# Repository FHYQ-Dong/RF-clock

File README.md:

# RF-clock

Two RFSoC 4x2 nodes, each with an SRS FS725 rubidium standard, exchange 5.8 GHz PRN bursts (two-way time transfer, TWTT). The follower steers its FS725 so that its 10 MHz and 1PPS follow the master. The PL keeps time and runs the per-burst measurement chain; the ARM runs the slower algorithms.

New to the project, or to RFSoC and clock measurement: start with the technical report, [docs/technical_report.md](docs/technical_report.md) ([中文](docs/technical_report_zh.md)).

English documents are the reference; `*_zh.md` files are Chinese translations with the same content.

## How it works

- **TWTT.** Nodes A (master) and B (follower) send each other known PRN bursts in fixed slots after each PPS. Each node timestamps the other's burst; differencing the two directions cancels the propagation delay and leaves the clock offset, which drives B's FS725 through its RS-232 port.
- **All of a node's clocks from its FS725.** The FS725 10 MHz drives the board's LMK04828 and LMX2594, which clock the RFDC converters and the PL. The PL counts a raw tick (100 MHz, 10 ns) on that clock, so steering the FS725 moves all of the node's clocks.
- **ARM does algorithms, PL does time and the per-burst measurement chain.** In the PL: the raw tick, PPS capture, the 2 ms slot engine, gap-free TX bursts made from chip sequences through the RRC filter starting at an exact tick, correlation (tracking and search) in every RX window, the measurement packets that carry each node's results to the other inside its bursts, the output PPS, and since 2.5, when chosen, each step of the steering through FC with its command on B's FS725's serial line. On the ARM (Python): the PRN chips and RRC coefficients, clock and RFDC bring-up, acquisition on long windows in DDR, the two-way equations, the steering algorithms that steer B's FS725, and the coefficient tables when the PL steers.
- **Signal.** BPSK PRN at 100 Mchip/s with an RRC filter (β = 0.25), 8 samples per chip at 800 MS/s complex baseband. The DAC runs at 9.6 GS/s and puts the burst at 5.8 GHz (second Nyquist zone); the ADC samples at 4.8 GS/s. RFDC multi-tile sync makes the converter latency the same on every power-up.

The design is in [plan/RF_clock_modules.md](plan/RF_clock_modules.md); the durable constraints any change must respect are in [AGENTS.md](AGENTS.md).

## Status

| Milestone | Result |
| --- | --- |
| M1: raw tick against the FS725 1PPS | Passed: exactly 100,000,000 ticks per second; 3 hours with no PPS jitter or fault count |
| M2: MTS and PPS-timed TX | Passed: every burst starts at its target tick; on a scope the PPS → burst delay is 180.00 ns on every restart |
| M3: wired DAC → ADC loopback | Passed with a cable and attenuator: with both LMX2594 synchronized and their VCO bands forced, the loopback delay holds to 0.1 ps over clock writes and 2.5 hours |
| M4: two-way time transfer between two boards on one reference | θ measured 250 times a second, 0.8 ps per measurement; θ₀ per wiring in `links/` |
| M5: two clocks, B's FS725 steered | θ − θ₀ 5.3–5.6 ps rms per second, steering through FC (2.3.0.2); B's output PPS against A's 9.2 ps rms per second on the scope, the scope's own resolution |
| M6: air link across Long Island Sound | Not started |

Item-by-item results with their evidence: [plan/checklist.md](plan/checklist.md). Results, what limits them and what remains: [docs/technical_report.md](docs/technical_report.md) sections 6–8.

## Hardware

Per node:

| Item | Connection |
| --- | --- |
| Real Digital RFSoC 4x2, PYNQ 3.1.1 image | the board's Linux runs the Python package as root |
| SRS FS725 10 MHz | external reference SMA of the 4x2 (LMK04828 CLKin0) |
| SRS FS725 1PPS | PPS SMA J7 (the board's comparator input) |
| B's FS725 RS-232, for the steering in the PL (2.5) | a TTL-to-RS-232 module (MAX3232, DB-9 male) on J1, the Pmod header, lower row at the PMODB end ([docs/board_setup.md](docs/board_setup.md) section 5.1) |
| RF transmit | DAC_A SMA (`vout20`, DAC tile 2) |
| RF receive | ADC_B SMA (`vin2_01`, ADC tile 2) |
| Loopback test (M3) | DAC_A → SMA cable → ≥ 20 dB attenuator → ADC_B |

Building the bitstream needs Vivado 2024.1 and the [RealDigitalOrg RFSoC4x2-BSP](https://github.com/RealDigitalOrg/RFSoC4x2-BSP) board files.

## Getting started

### On the board

Releases (on GitHub and on the group's Gitea) carry a wheel that contains the library, the bitstream, the clock register files, the examples and the board checks; nothing else from the repository is needed. Install the wheel into PYNQ's own environment as described in [docs/ABI.md §9.1](docs/ABI.md), then, as root:

```bash
run="sudo env BOARD=RFSoC4x2 XILINX_XRT=/usr /usr/local/share/pynq-venv/bin/python"
$run -m rf_clock.checks.vco_bands scan --write  # once per board: the board config,
$run -m rf_clock.checks.mts_dtc record --write   # then its MTS capture windows
$run -m rf_clock.checks.m1_check 60             # tick against the PPS
$run -m rf_clock.checks.m2_tx_timing 10         # MTS and timed bursts
$run -m rf_clock.checks.m3_loopback 20          # loopback delay by correlation
$run -m rf_clock.examples.pl.03_pynq_bringup    # one burst and one RX window
```

The board config, `/etc/rf-clock/board.json`, names its board by serial number and fixes the VCO band of each LMX2594 and the SYSREF capture window of each MTS tile, which otherwise can change from one power-up to the next and move a converter by 8-10 ps or by a whole sample; without them `PL.open()` warns ([docs/ABI.md §11.1](docs/ABI.md)).

A new board, from the SD card to the two-way time transfer, step by step with what each step must show: [docs/board_setup.md](docs/board_setup.md).

In your own code:

```python
from rf_clock.pl import PL, WaveformGenerator

pl = PL.open()                                  # overlay, clocks, MTS, PPS lock
beats = WaveformGenerator().generate_beats()
pl.tx_buffer.write_beats(beats)
_, pps = pl.ctrl.wait_next_pps()
target = pps + 100_000_000 + 100_000            # 1 ms after the next PPS
pl.ctrl.arm_tx(target, len(beats))
pl.ctrl.wait_tx(timeout=2.5)                    # returns TX_ACTUAL == target
```

### On a development machine

```bash
uv sync                               # Python environment (pynq is a dev dependency, for completion only)
uv run pytest                         # unit tests against a fake PL, no hardware
uv run pyright                        # static type check of src, tests, experiments and tools
uv run python -m rf_clock.examples.pl.01_fake_tx
./PL/sim/run_pl_tests.ps1             # RTL testbenches (PowerShell, iverilog)
```

### Building and releasing

1. Set the version in `pyproject.toml` (rules below).
2. On the build machine: `vivado -mode batch -source PL/bd/create_rf_clock_bd.tcl -tclargs <new build dir> <RFSoC4x2-BSP>/board_files impl`
3. `python3 tools/package_overlay.py <build dir>` copies the bitstream and a manifest into `src/rf_clock/overlay/` (refused unless the build completed with timing met for this version).
4. `uv run pytest` and `uv run pyright` pass; commit, then push a tag `vA.B.C.D`: GitHub Actions, and Gitea Actions where the tag is pushed to Gitea, build the wheel and publish a release with notes.

Details in [docs/ABI.md §14.1](docs/ABI.md).

### Versions

The package version `A.B.C.D` binds the Python code to its bitstream:

| Field | Meaning |
| --- | --- |
| A.B | register protocol version (`VERSION` in the PL) |
| C | which bitstream for that protocol |
| D | Python-only releases |

The build writes the version into the bitstream (`BUILD_VERSION`), and `PL.open()` refuses a bitstream whose A.B.C differs from the installed package. A rebuild increments C; a Python-only change increments D.

## Documents

| Document | Content |
| --- | --- |
| [docs/technical_report.md](docs/technical_report.md) ([中文](docs/technical_report_zh.md)) | Technical report and handoff, for readers new to RFSoC and clock measurement: background, design, bench, running and maintaining it, results, the problems found, open work. `pwsh -NoProfile -File tools/build_report.ps1` makes its PDF in `build/` |
| [AGENTS.md](AGENTS.md) | Durable design constraints |
| [plan/RF_clock_modules.md](plan/RF_clock_modules.md) ([中文](plan/RF_clock_modules_zh.md)) | Design plan |
| [plan/checklist.md](plan/checklist.md) ([中文](plan/checklist_zh.md)) | Open items, with evidence for each closed one |
| [docs/ABI.md](docs/ABI.md) ([中文](docs/ABI_zh.md)) | ARM ↔ PL programming manual: registers, timing, power-up, the Python library, board setup, releases |
| [docs/handoff_2x.md](docs/handoff_2x.md) ([中文](docs/handoff_2x_zh.md)) | Moving from 1.x to 2.x: what changed, how to run the link, the metrics before and after and what improved them |
| [docs/board_setup.md](docs/board_setup.md) ([中文](docs/board_setup_zh.md)) | From a new board to one in service: system, installation, wiring, the checks and per-board calibrations in order, what to redo after a change |
| [docs/debug_overview.md](docs/debug_overview.md) ([中文](docs/debug_overview_zh.md)) | Every problem found on the bench, along the 10 MHz distribution: a diagram of each module marking where the problems sat; what was seen, the cause, the change and the version, with links to the reports |
| [src/rf_clock/clocks/files/README.md](src/rf_clock/clocks/files/README.md) | Clock plan and the LMK/LMX register files |

## Layout

| Path | Content |
| --- | --- |
| `PL/src/` | PL RTL (`p_top` and P0–P13); `p_regs.vh` / `p_defs.vh` define the ARM-visible interface |
| `PL/sim/` | iverilog testbenches; run `./PL/sim/run_pl_tests.ps1` |
| `PL/bd/create_rf_clock_bd.tcl` | Vivado 2024.1 block design, synthesis and implementation |
| `PL/constraints/` | RFSoC 4x2 constraints |
| `src/rf_clock/pl/` | ARM ↔ PL interface: power-up, registers, the board config, the slot engine, bursts from chips, the correlator's tracking and search, the measurement queue, acquisition, the output PPS, the FS725's serial line, the steering in the PL; TX buffer, RX DMA, beat codec, waveform generator |
| `src/rf_clock/clocks/` | LMK04828/LMX2594 register files and their decoders |
| `src/rf_clock/overlay/` | The bitstream (`.bit`/`.hwh`/`.xsa`, Git LFS) shipped with the package |
| `src/rf_clock/checks/` | Board checks for milestones M1–M3, one node of the rf-clock 2 link (`m4c_link`), the per-board calibrations (`vco_bands`, `mts_dtc`, `fs725_loop`, `pps_pp_scan`) and the output PPS on its own (`pps_out`) |
| `src/rf_clock/examples/` | Annotated examples: fake PL, board bring-up, one node of the rf-clock 2 link, the two-way equations and the steering on a development machine, raw PYNQ and C++ access |
| `src/rf_clock/correlator.py` | Cross-correlation delay estimation |
| `src/rf_clock/plmodel/` | Bit-exact models of the PL's measurement chain and of its steering through FC, for the RTL testbenches and to recompute the PL's results on the ARM |
| `src/rf_clock/twtt/` | Two-way time transfer between two boards: rf-clock 2's two-way equations from a node's queue (`pairs`), the node's FS725 and SYNCED (`control`), the steering algorithms that steer B's FS725 (`steer`), the node's log read back (`logs`); the 1.x exchange over Ethernet (`timing`, `node`, `link`) |
| `src/rf_clock/fs725.py` | The FS725 rubidium standard over RS-232: status, frequency offset (SF), loop gain (GA), the crystal's tuning (FC), 1 pps time tags and placement |
| `tests/` | Unit tests (pytest, no hardware) |
| `tools/` | ABI generator, overlay packaging, release notes, version snapshots, results backup, the technical report's PDF, JTAG board reset |
| `boards/` | A copy of each board's config (`/etc/rf-clock/board.json`): reference and backup |
| `links/` | θ₀, B's steering target, per pair of boards and wiring ([links/README.md](links/README.md)) |
| `experiments/` | Bench experiments, run on RF-clock-PC: `m<N>_*.py` is a sub-experiment of milestone M<N> (plan section 9), one question each; `m3_common.py` holds what the M3 loopback series share; `epg1.py`, `lnb.py`, `sa_sweep.py` are the bench tools they use (EPG1 PPS distribution, scope .lnb files, SA124B) |
| `.github/workflows/release.yml` | Builds and publishes a GitHub release when a `vA.B.C.D` tag is pushed |
| `.gitea/workflows/release.yml` | The same for a Gitea release, plus an upload to the Gitea PyPI registry (Gitea Actions) |

The bitstream and other binaries are stored with Git LFS: after cloning, run `git lfs install` and `git lfs pull`.

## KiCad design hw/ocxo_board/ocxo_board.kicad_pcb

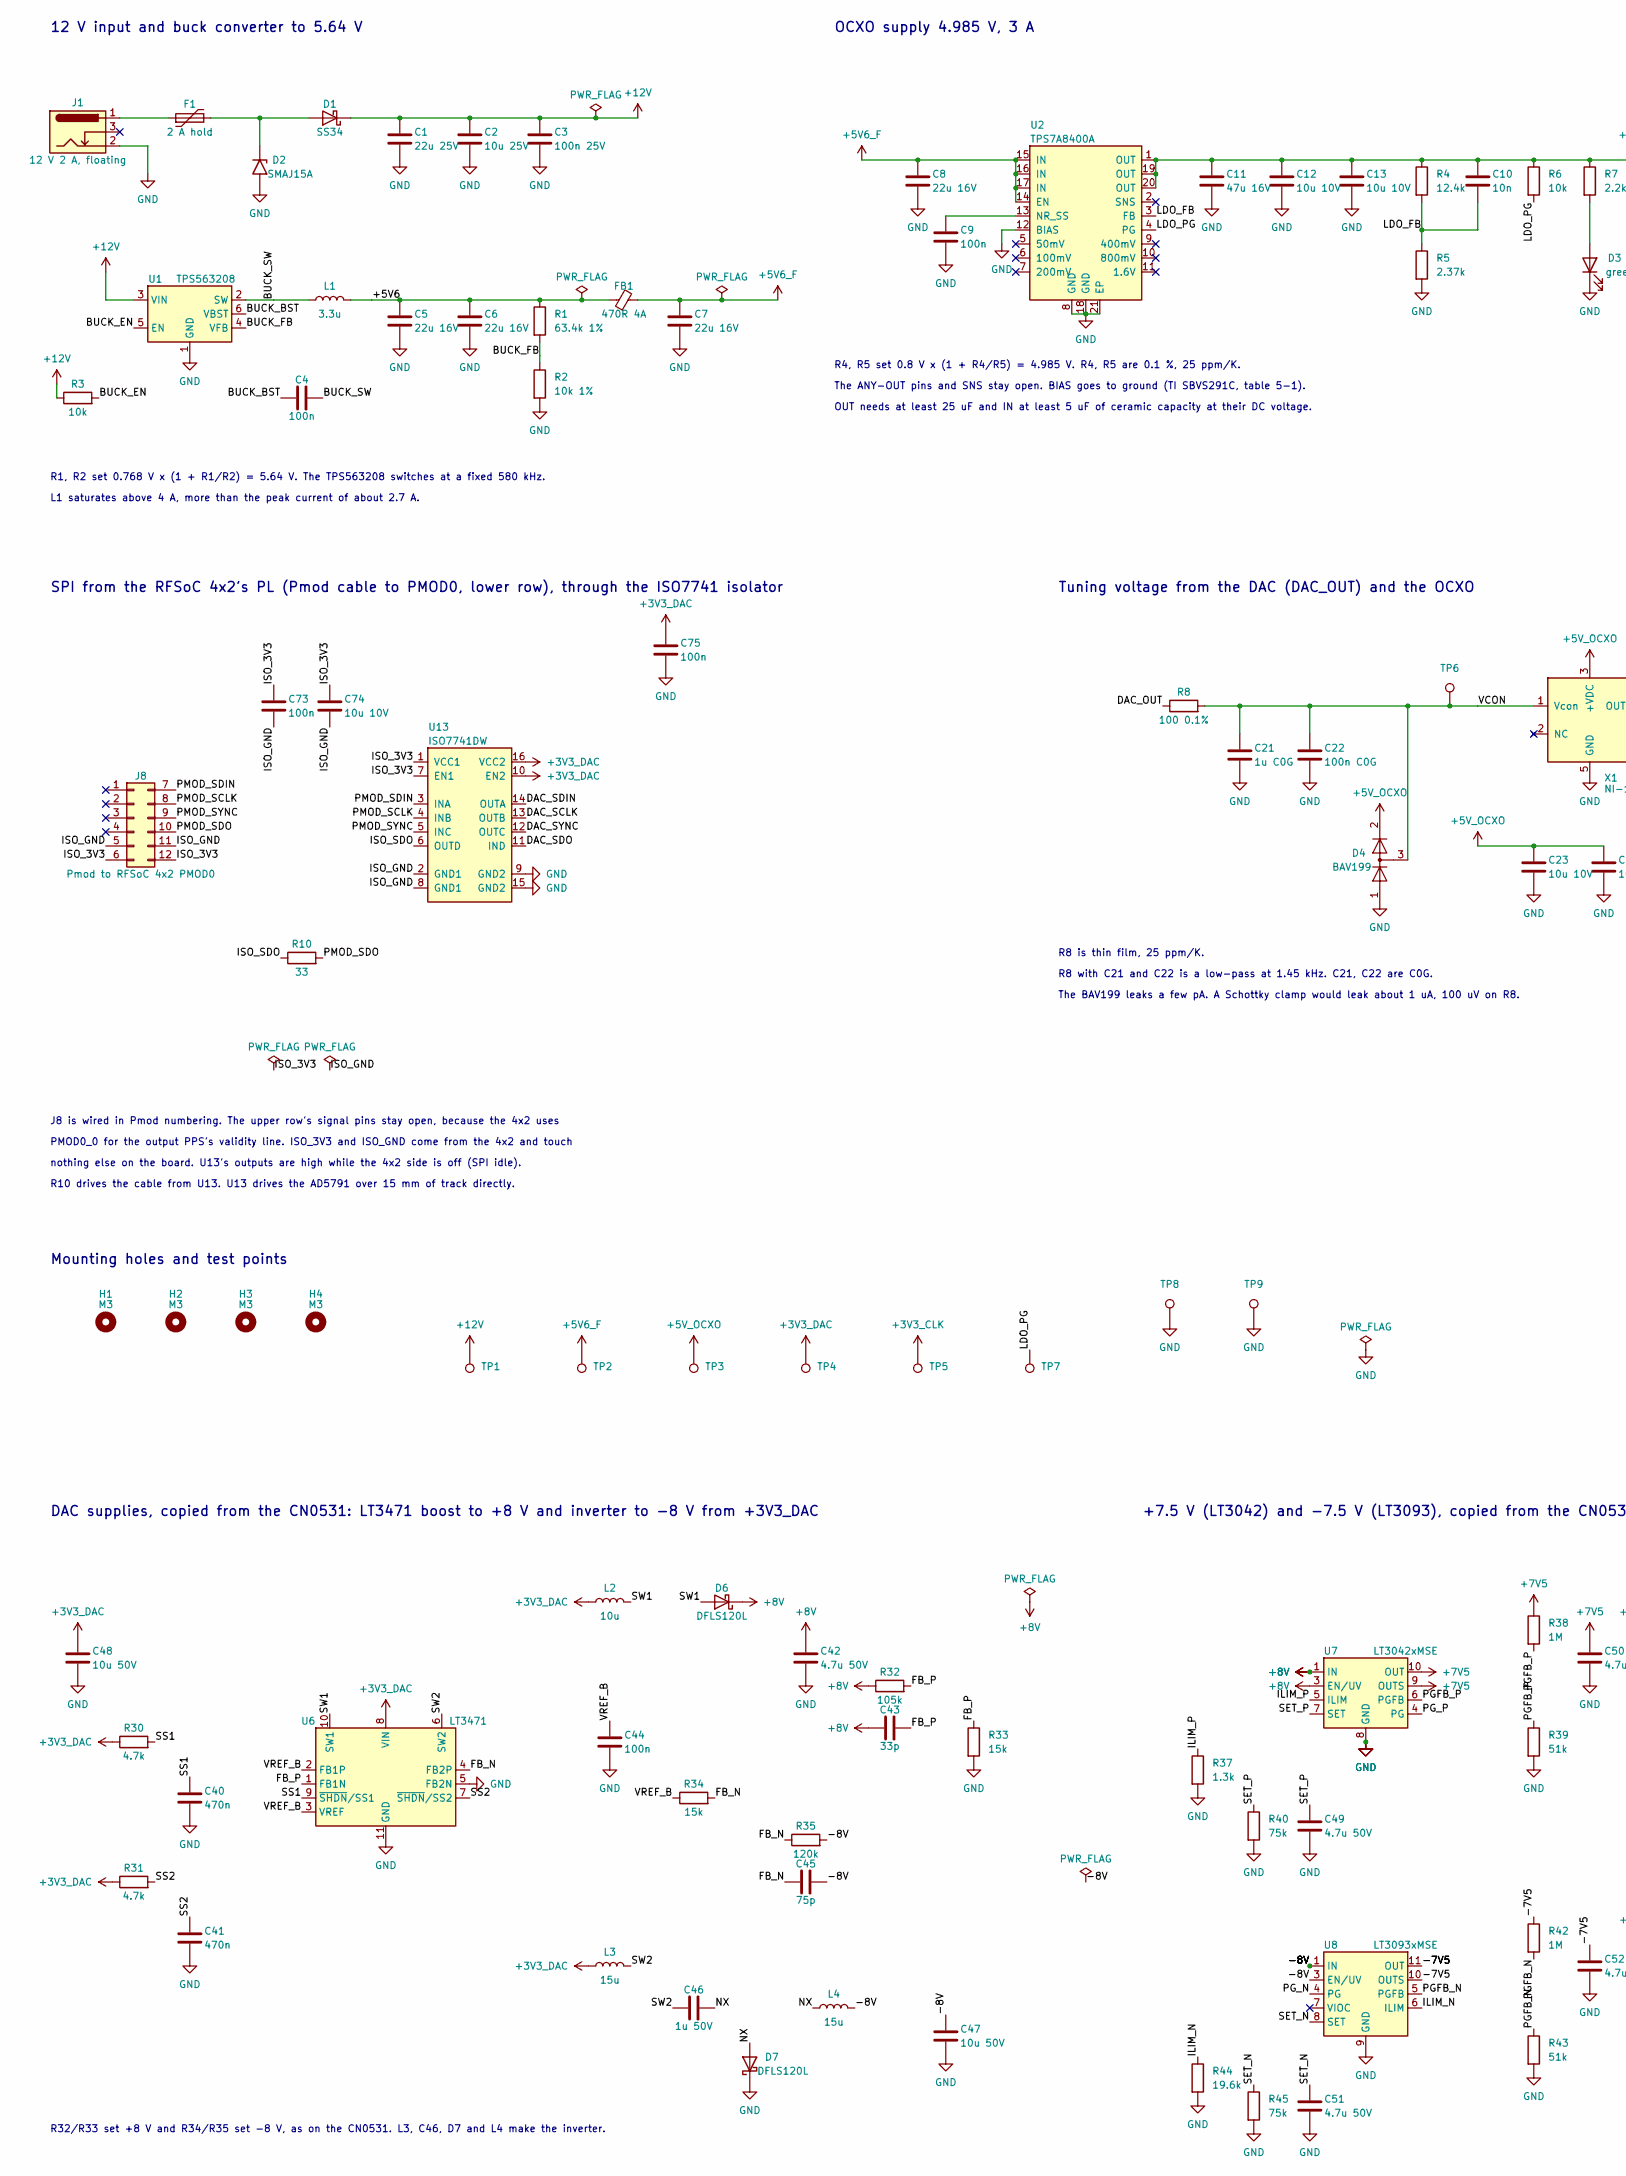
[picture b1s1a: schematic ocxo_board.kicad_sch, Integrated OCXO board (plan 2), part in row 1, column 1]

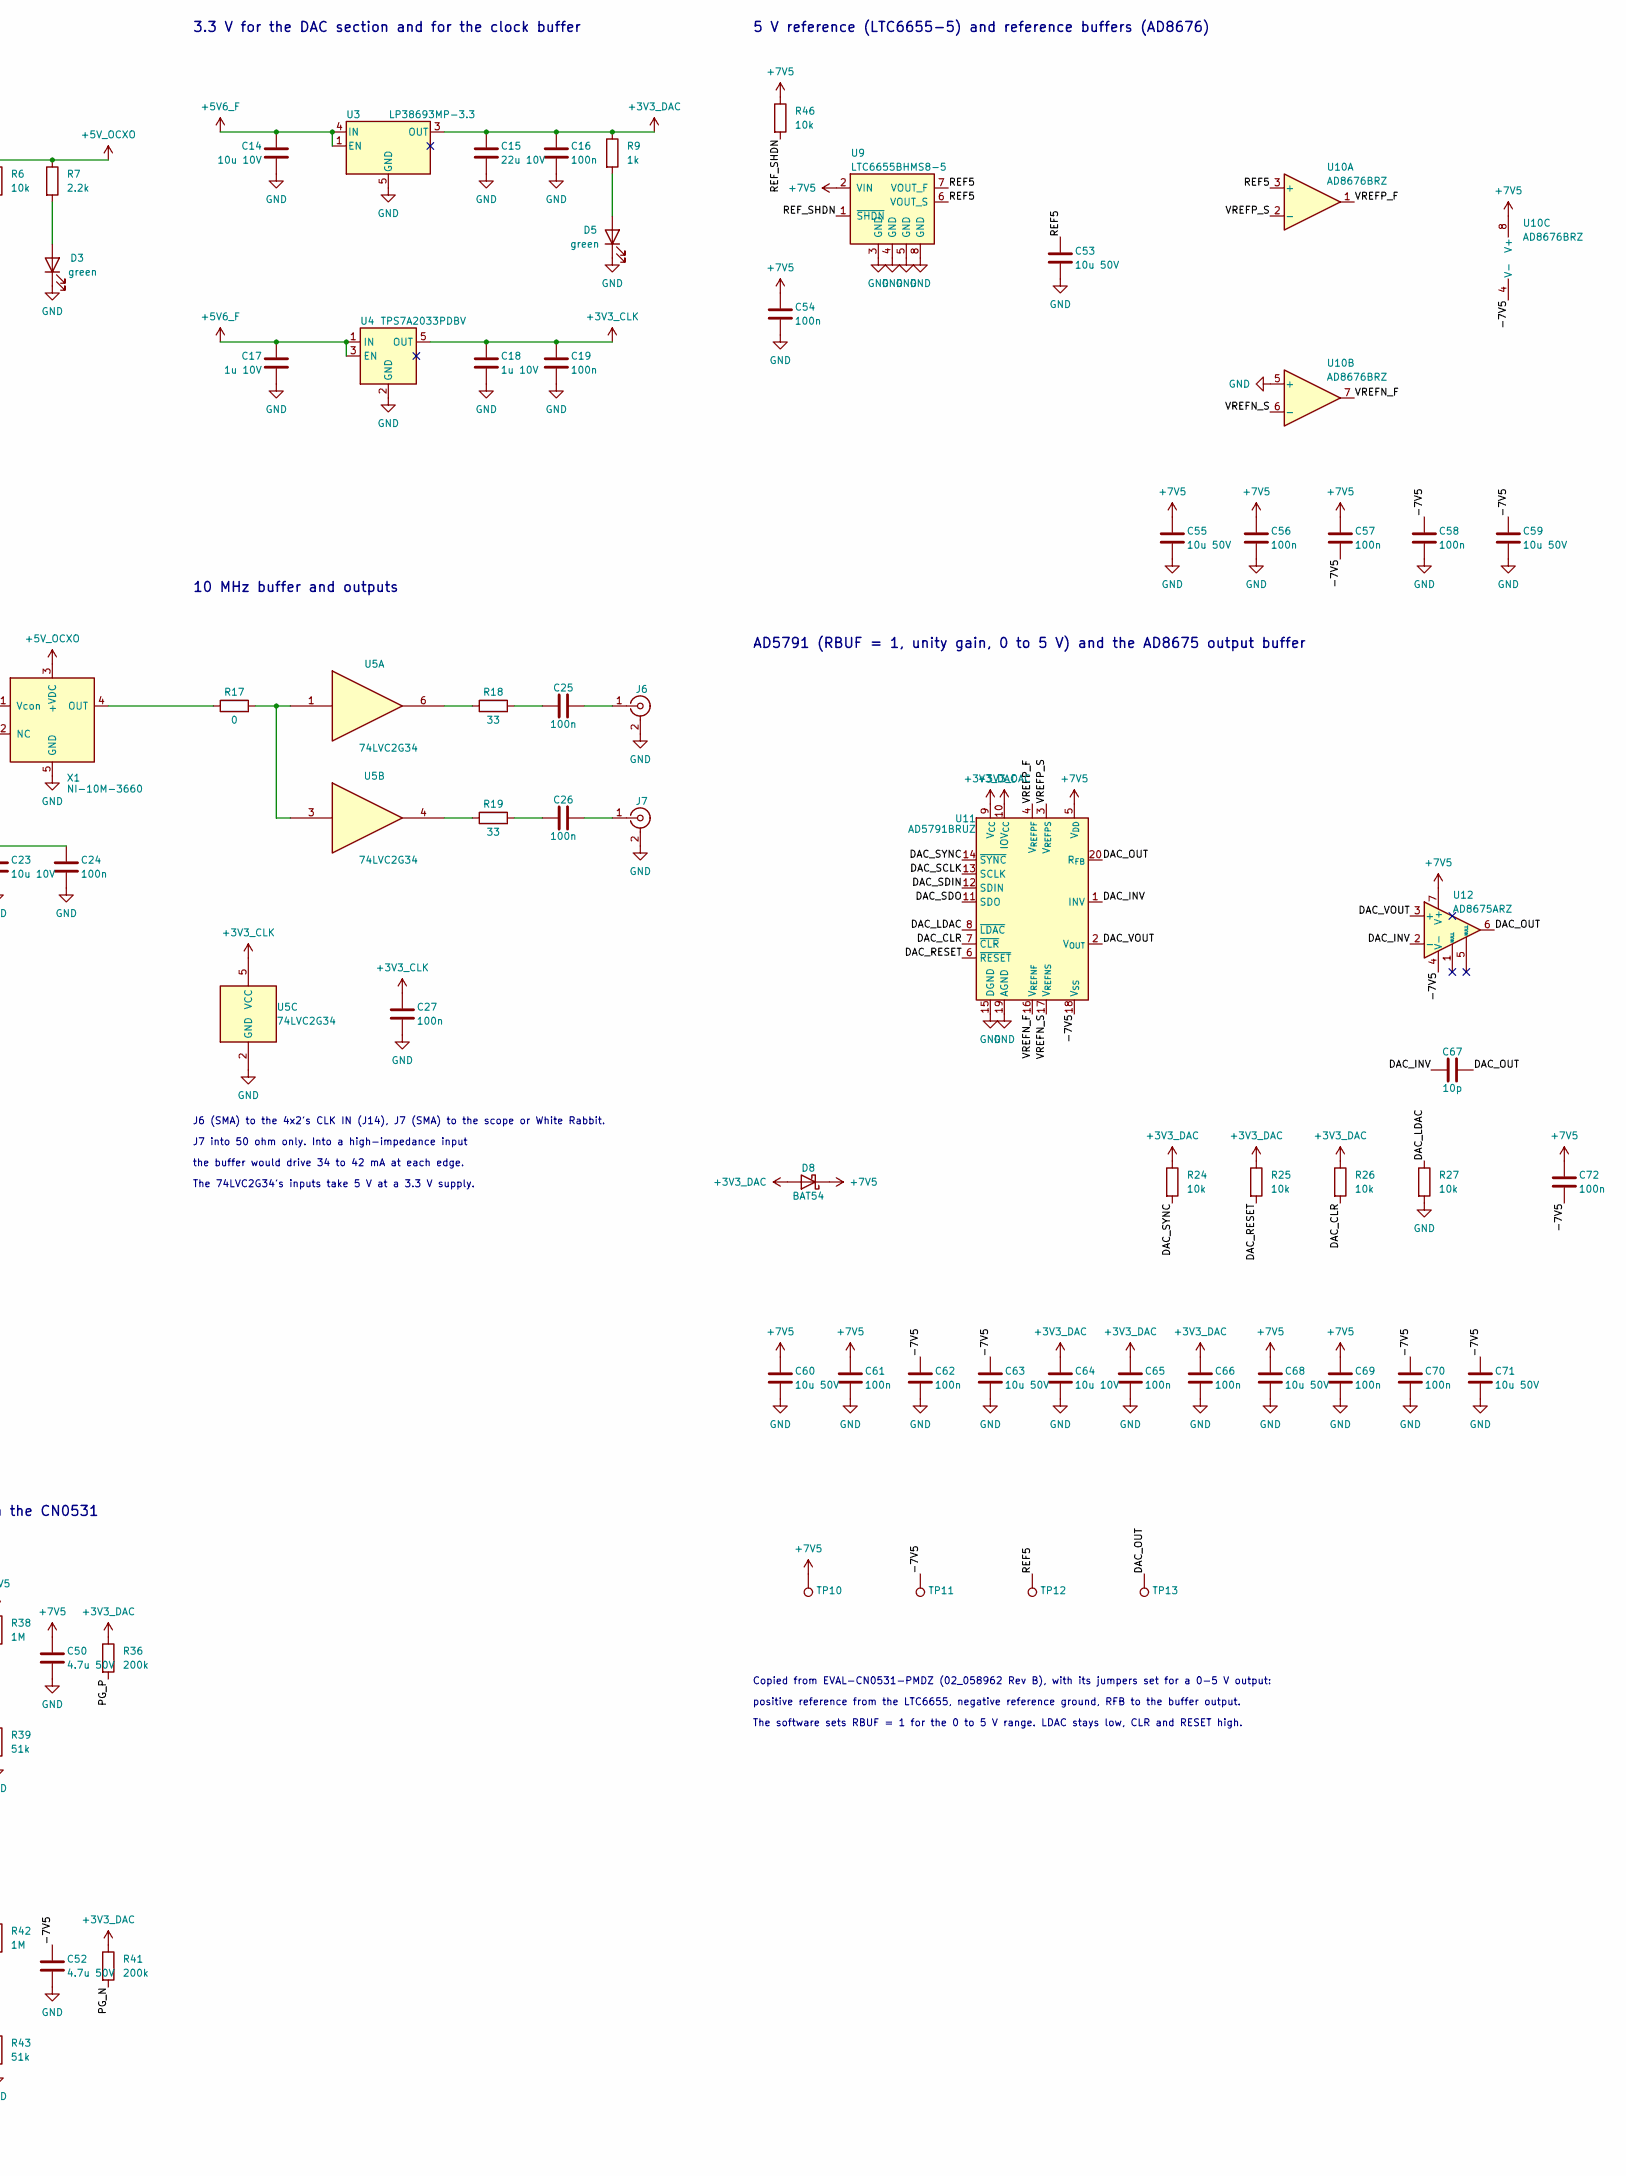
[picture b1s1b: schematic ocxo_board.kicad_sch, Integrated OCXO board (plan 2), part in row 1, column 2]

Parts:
C1: 22u 25V; C_1206_3216Metric; MPN CL31A226KAHNNNE; LCSC C12891
C2: 10u 25V; C_1206_3216Metric; MPN CL31A106KBHNNNE; LCSC C13585
C3: 100n 25V; C_0603_1608Metric; MPN CC0603KRX7R9BB104; LCSC C14663
C4, C9, C16, C19, C24, C25, C26, C27, C44, C54, C56, C57, C58, C61, C62, C65, C66, C69, C70, C72, C73, C75: 100n; C_0603_1608Metric; MPN CC0603KRX7R9BB104; LCSC C14663
C5, C6, C7, C8: 22u 16V; C_1206_3216Metric; MPN CL31A226KAHNNNE; LCSC C12891
C10: 10n; C_0603_1608Metric; MPN 0603B103K500NT; LCSC C57112
C11: 47u 16V; C_1210_3225Metric; MPN CL32A476MOJNNNE; LCSC C3039702
C12, C13, C14, C23, C64, C74: 10u 10V; C_0805_2012Metric; MPN CL21A106KAYNNNE; LCSC C15850
C15: 22u 10V; C_1206_3216Metric; MPN CL31A226KAHNNNE; LCSC C12891
C17, C18: 1u 10V; C_0603_1608Metric; MPN CL10A105KB8NNNC; LCSC C15849
C21: 1u C0G; C_1210_3225Metric; MPN C3225C0G1E105J250AC
C22: 100n C0G; C_0805_2012Metric; MPN GRM21B5C1H104JA01L
C40, C41: 470n; C_0603_1608Metric; MPN CL10B474KA8NNNC; LCSC C1623
C42, C49, C50, C51, C52: 4.7u 50V; C_1206_3216Metric; MPN 1206B475K500NT; LCSC C29823
C43: 33p; C_0603_1608Metric; MPN CL10C330JB8NNNC; LCSC C1663
C45: 75p; C_0603_1608Metric; MPN 0603CG750J500NT; LCSC C1681
C46: 1u 50V; C_0603_1608Metric; MPN CL10A105KB8NNNC; LCSC C15849
C47, C48, C53, C55, C59, C60, C63, C68, C71: 10u 50V; C_1206_3216Metric; MPN CL31A106KBHNNNE; LCSC C13585
C67: 10p; C_0603_1608Metric; MPN CL10C100JB8NNNC; LCSC C1634
D1: SS34; D_SMA; MPN SS34; LCSC C8678
D2: SMAJ15A; D_SMA; MPN SMAJ15A; LCSC C5353166
D3, D5: green; LED_0603_1608Metric; MPN 19-217/G7C-AN1P2/6T; LCSC C2986030
D4: BAV199; SOT-23; MPN BAV199,215; LCSC C40919
D6, D7: DFLS120L; D_PowerDI-123; MPN DFLS120L-7; LCSC C155287
D8: BAT54; D_SOD-323; MPN LBAT54HT1G; LCSC C12744
F1: 2 A hold; Fuse_1812_4532Metric; MPN ASMD1812-200-30V; LCSC C2982282
FB1: 470R 4A; L_1206_3216Metric; MPN BLM31KN471SN1L; LCSC C703117
H1, H2, H3, H4: M3; MountingHole_3.2mm_M3
J1: 12 V 2 A, floating; BarrelJack_Horizontal; MPN DC-005-A200; LCSC C720557
J6, J7: SMA; SMA_Amphenol_132289_EdgeMount; MPN 132289
J8: Pmod to RFSoC 4x2 PMOD0; Pmod_Header_2x06_P2.54mm_Horizontal; MPN 2x6 male header, 2.54 mm, right angle
L1: 3.3u; L_Bourns_SRP5030T; MPN SRP5030T-3R3M; LCSC C189931
L2: 10u; L_Taiyo-Yuden_NR-40xx; MPN MNR4018T100MT; LCSC C18222009
L3, L4: 15u; L_Taiyo-Yuden_NR-40xx; MPN MNR4018T150MT; LCSC C20612490
R1: 63.4k 1%; R_0603_1608Metric; MPN FRC0603F6342TS; LCSC C2999593
R2: 10k 1%; R_0603_1608Metric; MPN 0603WAF1002T5E; LCSC C25804
R3, R6, R24, R25, R26, R27, R46: 10k; R_0603_1608Metric; MPN 0603WAF1002T5E; LCSC C25804
R4: 12.4k; R_0603_1608Metric; MPN RT0603BRD0712K4L; LCSC C861102
R5: 2.37k; R_0603_1608Metric; MPN RT0603BRD072K37L; LCSC C705759
R7: 2.2k; R_0603_1608Metric; MPN 0603WAF2201T5E; LCSC C4190
R8: 100 0.1%; R_0603_1608Metric; MPN TNPW0603100RBEEA; LCSC C844889
R9: 1k; R_0603_1608Metric; MPN 0603WAF1001T5E; LCSC C21190
R10, R18, R19: 33; R_0603_1608Metric; MPN 0603WAF330JT5E; LCSC C23140
R17: 0; R_0603_1608Metric; MPN 0603WAF0000T5E; LCSC C21189
R30, R31: 4.7k; R_0603_1608Metric; MPN 0603WAF4701T5E; LCSC C23162
R32: 105k; R_0603_1608Metric; MPN 0603WAF1053T5E; LCSC C16840
R33, R34: 15k; R_0603_1608Metric; MPN 0603WAF1502T5E; LCSC C22809
R35: 120k; R_0603_1608Metric; MPN 0603WAF1203T5E; LCSC C25808
R36, R41: 200k; R_0603_1608Metric; MPN 0603WAF2003T5E; LCSC C25811
R37: 1.3k; R_0603_1608Metric; MPN 0603WAF1301T5E; LCSC C22767
R38, R42: 1M; R_0603_1608Metric; MPN 0603WAF1004T5E; LCSC C22935
R39, R43: 51k; R_0603_1608Metric; MPN 0603WAF5102T5E; LCSC C23196
R40, R45: 75k; R_0603_1608Metric; MPN 0603WAF7502T5E; LCSC C23242
R44: 19.6k; R_0603_1608Metric; MPN 0603WAF1962T5E; LCSC C22898
TP1: +12V; TestPoint_Pad_D1.5mm
TP2: +5V6_F; TestPoint_Pad_D1.5mm
TP3: +5V_OCXO; TestPoint_Pad_D1.5mm
TP4: +3V3_DAC; TestPoint_Pad_D1.5mm
TP5: +3V3_CLK; TestPoint_Pad_D1.5mm
TP6: VCON; TestPoint_Pad_D1.5mm
TP7: LDO_PG; TestPoint_Pad_D1.5mm
TP8, TP9: GND loop; TestPoint_Keystone_5000-5004_Miniature; MPN 5001
TP10: +7V5; TestPoint_Pad_D1.5mm
TP11: -7V5; TestPoint_Pad_D1.5mm
TP12: REF5; TestPoint_Pad_D1.5mm
TP13: DAC_OUT; TestPoint_Pad_D1.5mm
U1: TPS563208; SOT-23-6; MPN TPS563208DDCR; LCSC C468250
U2: TPS7A8400A; QFN-20-1EP_3.5x3.5mm_P0.5mm_EP2x2mm_ThermalVias; MPN TPS7A8400ARGRR; LCSC C524802
U3: LP38693MP-3.3; SOT-223-5; MPN LP38693MP-3.3/NOPB; LCSC C130904
U4: TPS7A2033PDBV; SOT-23-5; MPN TPS7A2033PDBVR; LCSC C2862740
U5: 74LVC2G34; SOT-363_SC-70-6; MPN 74LVC2G34GW,125; LCSC C426709
U6: LT3471; DFN-10-1EP_3x3mm_P0.5mm_EP1.65x2.38mm; MPN LT3471EDD#TRPBF; LCSC C514422
U7: LT3042xMSE; MSOP-10-1EP_3x3mm_P0.5mm_EP1.68x1.88mm; MPN LT3042EMSE#TRPBF; LCSC C461518
U8: LT3093xMSE; MSOP-12-1EP_3x4.039mm_P0.65mm_EP1.651x2.845mm; MPN LT3093EMSE#PBF; LCSC C670482
U9: LTC6655BHMS8-5; MSOP-8_3x3mm_P0.65mm; MPN LTC6655BHMS8-5#PBF; LCSC C689432
U10: AD8676BRZ; SOIC-8_3.9x4.9mm_P1.27mm; MPN AD8676BRZ; LCSC C206590
U11: AD5791BRUZ; TSSOP-20_4.4x6.5mm_P0.65mm; MPN AD5791BRUZ; LCSC C578299
U12: AD8675ARZ; SOIC-8_3.9x4.9mm_P1.27mm; MPN AD8675ARZ; LCSC C207408
U13: ISO7741DW; SOIC-16W_7.5x10.3mm_P1.27mm; MPN ISO7741DWR; LCSC C571196
X1: NI-10M-3660; OCXO_Taitien_NI-10M-3600; MPN NI-10M-3660

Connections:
+3V3_CLK: C18.1, C19.1, C27.1, TP5.1, U4.5 (OUT), U5.5 (VCC)
+3V3_DAC: C15.1, C16.1, C48.1, C64.1, C65.1, C66.1, C75.1, D8.2 (A), L2.1, L3.1, R9.1, R24.1, R25.1, R26.1, R30.1, R31.1, R36.1, R41.1, TP4.1, U3.3 (OUT), U6.8 (VIN), U11.9 (V_{CC}), U11.10 (IOV_{CC}), U13.10 (EN2), U13.16 (VCC2)
+5V6_F: C7.1, C8.1, C14.1, C17.1, FB1.2, TP2.1, U2.14 (EN), U2.15 (IN), U2.16 (IN), U2.17 (IN), U3.1 (EN), U3.4 (IN), U4.1 (IN), U4.3 (EN)
+5V_OCXO: C10.1, C11.1, C12.1, C13.1, C23.1, C24.1, D4.2 (A), R4.1, R6.1, R7.1, TP3.1, U2.1 (OUT), U2.19 (OUT), U2.20 (OUT), X1.3 (+VDC)
+7V5: C50.1, C54.1, C55.1, C56.1, C57.1, C60.1, C61.1, C68.1, C69.1, C72.1, D8.1 (K), R38.1, R46.1, TP10.1, U7.9 (OUTS), U7.10 (OUT), U9.2 (VIN), U10.8 (V+), U11.5 (V_{DD}), U12.7 (V+)
+8V: C42.1, C43.1, D6.1 (K), R32.1, U7.1 (IN), U7.2 (IN), U7.3 (EN/UV)
+12V: C1.1, C2.1, C3.1, D1.1 (K), R3.1, TP1.1, U1.3 (VIN)
/+5V6: C5.1, C6.1, FB1.1, L1.2, R1.1
/-7V5: C52.1, C57.2, C58.1, C59.1, C62.1, C63.1, C70.1, C71.1, C72.2, R42.1, TP11.1, U8.10 (OUTS), U8.11 (OUT), U8.12 (OUT), U10.4 (V-), U11.18 (V_{SS}), U12.4 (V-)
/-8V: C45.2, C47.1, L4.2, R35.2, U8.1 (IN), U8.2 (IN), U8.3 (EN/UV), U8.13 (IN)
/BUCK_BST: C4.1, U1.6 (VBST)
/BUCK_EN: R3.2, U1.5 (EN)
/BUCK_FB: R1.2, R2.1, U1.4 (VFB)
/BUCK_SW: C4.2, L1.1, U1.2 (SW)
/DAC_CLR: R26.2, U11.7 (~CLR)
/DAC_INV: C67.1, U11.1 (INV), U12.2 (-)
/DAC_LDAC: R27.1, U11.8 (~LDAC)
/DAC_OUT: C67.2, R8.1, TP13.1, U11.20 (R_{FB}), U12.6
/DAC_RESET: R25.2, U11.6 (~RESET)
/DAC_SCLK: U11.13 (SCLK), U13.13 (OUTB)
/DAC_SDIN: U11.12 (SDIN), U13.14 (OUTA)
/DAC_SDO: U11.11 (SDO), U13.11 (IND)
/DAC_SYNC: R24.2, U11.14 (~SYNC), U13.12 (OUTC)
/DAC_VOUT: U11.2 (V_{OUT}), U12.3 (+)
/FB_N: C45.1, R34.2, R35.1, U6.4 (FB2P)
/FB_P: C43.2, R32.2, R33.1, U6.1 (FB1N)
/ILIM_N: R44.1, U8.6 (ILIM)
/ILIM_P: R37.1, U7.5 (ILIM)
/ISO_3V3: C73.1, C74.1, J8.6, J8.12, U13.1 (VCC1), U13.7 (EN1)
/ISO_GND: C73.2, C74.2, J8.5, J8.11, U13.2 (GND1), U13.8 (GND1)
/ISO_SDO: R10.1, U13.6 (OUTD)
/LDO_FB: C10.2, R4.2, R5.1, U2.3 (FB)
/LDO_PG: R6.2, TP7.1, U2.4 (PG)
/NX: C46.2, D7.2 (A), L4.1
/PGFB_N: R42.2, R43.1, U8.5 (PGFB)
/PGFB_P: R38.2, R39.1, U7.6 (PGFB)
/PG_N: R41.2, U8.4 (PG)
/PG_P: R36.2, U7.4 (PG)
/PMOD_SCLK: J8.8, U13.4 (INB)
/PMOD_SDIN: J8.7, U13.3 (INA)
/PMOD_SDO: J8.10, R10.2
/PMOD_SYNC: J8.9, U13.5 (INC)
/REF5: C53.1, TP12.1, U9.6 (VOUT_S), U9.7 (VOUT_F), U10.3 (+)
/REF_SHDN: R46.2, U9.1 (~SHDN)
/SET_N: C51.1, R45.1, U8.8 (SET)
/SET_P: C49.1, R40.1, U7.7 (SET)
/SS1: C40.1, R30.2, U6.9 (~SHDN/SS1)
/SS2: C41.1, R31.2, U6.7 (~SHDN/SS2)
/SW1: D6.2 (A), L2.2, U6.10 (SW1)
/SW2: C46.1, L3.2, U6.6 (SW2)
/VCON: C21.1, C22.1, D4.3 (K), R8.2, TP6.1, X1.1 (Vcon)
/VREFN_F: U10.7, U11.16 (V_{REFNF})
/VREFN_S: U10.6 (-), U11.17 (V_{REFNS})
/VREFP_F: U10.1, U11.4 (V_{REFPF})
/VREFP_S: U10.2 (-), U11.3 (V_{REFPS})
/VREF_B: C44.1, R34.1, U6.2 (FB1P), U6.3 (VREF)
GND: C1.2, C2.2, C3.2, C5.2, C6.2, C7.2, C8.2, C9.2, C11.2, C12.2, C13.2, C14.2, C15.2, C16.2, C17.2, C18.2, C19.2, C21.2, C22.2, C23.2, C24.2, C27.2, C40.2, C41.2, C42.2, C44.2, C47.2, C48.2, C49.2, C50.2, C51.2, C52.2, C53.2, C54.2, C55.2, C56.2, C58.2, C59.2, C60.2, C61.2, C62.2, C63.2, C64.2, C65.2, C66.2, C68.2, C69.2, C70.2, C71.2, C75.2, D2.2 (A2), D3.1 (K), D4.1 (K), D5.1 (K), D7.1 (K), J1.2, J6.2 (Ext), J7.2 (Ext), R2.2, R5.2, R27.2, R33.2, R37.2, R39.2, R40.2, R43.2, R44.2, R45.2, TP8.1, TP9.1, U1.1 (GND), U2.8 (GND), U2.12 (BIAS), U2.18 (GND), U2.21 (EP), U3.5 (GND), U4.2 (GND), U5.2 (GND), U6.5 (FB2N), U6.11 (GND), U7.8 (GND), U7.11 (GND), U8.9 (GND), U9.3 (GND), U9.4 (GND), U9.5 (GND), U9.8 (GND), U10.5 (+), U11.15 (DGND), U11.19 (AGND), U13.9 (GND2), U13.15 (GND2), X1.5 (GND)
unnamed: C25.1, R18.2
unnamed: C26.1, R19.2
unnamed: D1.2 (A), D2.1 (A1), F1.2
unnamed: D3.2 (A), R7.2
unnamed: D5.2 (A), R9.2
unnamed: F1.1, J1.1
unnamed: C25.2, J6.1 (In)
unnamed: C26.2, J7.1 (In)
unnamed: R17.2, U5.1, U5.3
unnamed: R18.1, U5.6
unnamed: R19.1, U5.4
unnamed: C9.1, U2.13 (NR_SS)
unnamed: R17.1, X1.4 (OUT)

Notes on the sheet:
12 V input and buck converter to 5.64 V
R1, R2 set 0.768 V x (1 + R1/R2) = 5.64 V. The TPS563208 switches at a fixed 580 kHz.
L1 saturates above 4 A, more than the peak current of about 2.7 A.
OCXO supply 4.985 V, 3 A
R4, R5 set 0.8 V x (1 + R4/R5) = 4.985 V. R4, R5 are 0.1 %, 25 ppm/K.
The ANY-OUT pins and SNS stay open. BIAS goes to ground (TI SBVS291C, table 5-1).
OUT needs at least 25 uF and IN at least 5 uF of ceramic capacity at their DC voltage.
3.3 V for the DAC section and for the clock buffer
Tuning voltage from the DAC (DAC_OUT) and the OCXO
R8 is thin film, 25 ppm/K.
R8 with C21 and C22 is a low-pass at 1.45 kHz. C21, C22 are C0G.
The BAV199 leaks a few pA. A Schottky clamp would leak about 1 uA, 100 uV on R8.
10 MHz buffer and outputs
J6 (SMA) to the 4x2's CLK IN (J14), J7 (SMA) to the scope or White Rabbit.
J7 into 50 ohm only. Into a high-impedance input
the buffer would drive 34 to 42 mA at each edge.
The 74LVC2G34's inputs take 5 V at a 3.3 V supply.
Mounting holes and test points
DAC supplies, copied from the CN0531: LT3471 boost to +8 V and inverter to -8 V from +3V3_DAC
R32/R33 set +8 V and R34/R35 set -8 V, as on the CN0531. L3, C46, D7 and L4 make the inverter.
+7.5 V (LT3042) and -7.5 V (LT3093), copied from the CN0531
5 V reference (LTC6655-5) and reference buffers (AD8676)
AD5791 (RBUF = 1, unity gain, 0 to 5 V) and the AD8675 output buffer
Copied from EVAL-CN0531-PMDZ (02_058962 Rev B), with its jumpers set for a 0-5 V output:
positive reference from the LTC6655, negative reference ground, RFB to the buffer output.
The software sets RBUF = 1 for the 0 to 5 V range. LDAC stays low, CLR and RESET high.
SPI from the RFSoC 4x2's PL (Pmod cable to PMOD0, lower row), through the ISO7741 isolator
J8 is wired in Pmod numbering. The upper row's signal pins stay open, because the 4x2 uses
PMOD0_0 for the output PPS's validity line. ISO_3V3 and ISO_GND come from the 4x2 and touch
nothing else on the board. U13's outputs are high while the 4x2 side is off (SPI idle).
R10 drives the cable from U13. U13 drives the AD5791 over 15 mm of track directly.

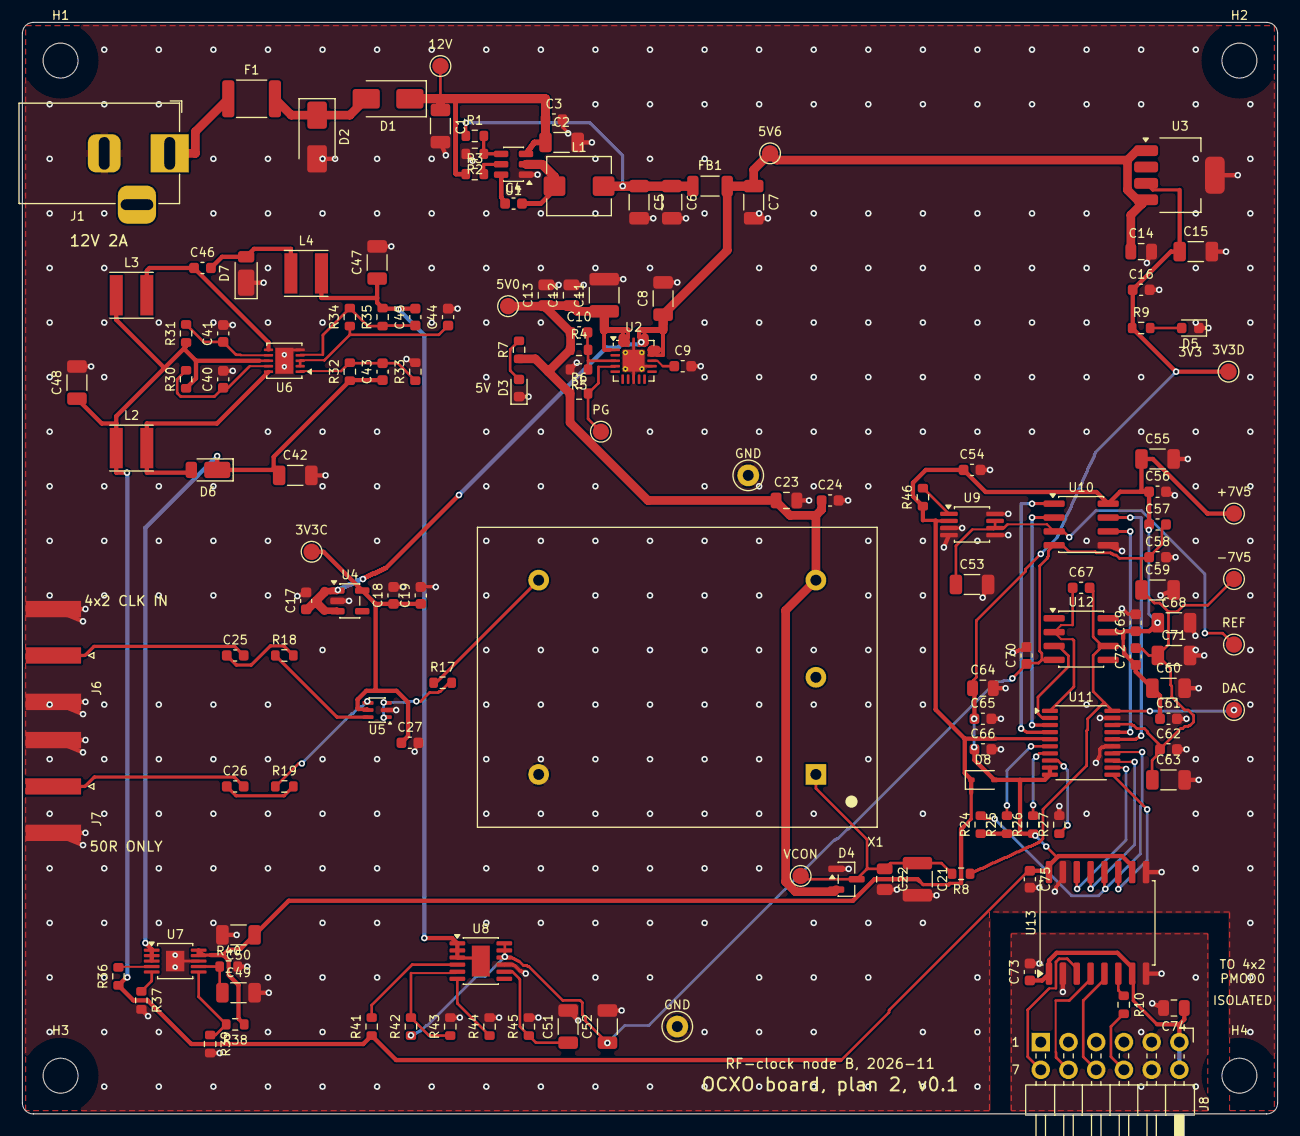
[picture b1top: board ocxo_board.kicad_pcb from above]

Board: 4 copper layers, 115.0 x 100.0 mm, 145 parts (0 on the bottom side), 70 nets.

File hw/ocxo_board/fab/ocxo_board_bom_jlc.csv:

Comment,Designator,Footprint,LCSC Part #,Manufacturer Part Number
22u 25V / 22u 16V / 22u 10V,"C1,C5,C6,C7,C8,C15",C_1206_3216Metric,C12891,CL31A226KAHNNNE
10u 25V / 10u 50V,"C2,C47,C48,C53,C55,C59,C60,C63,C68,C71",C_1206_3216Metric,C13585,CL31A106KBHNNNE
100n 25V / 100n,"C3,C4,C9,C16,C19,C24,C25,C26,C27,C44,C54,C56,C57,C58,C61,C62,C65,C66,C69,C70,C72,C73,C75",C_0603_1608Metric,C14663,CC0603KRX7R9BB104
10n,C10,C_0603_1608Metric,C57112,0603B103K500NT
47u 16V,C11,C_1210_3225Metric,C3039702,CL32A476MOJNNNE
10u 10V,"C12,C13,C14,C23,C64,C74",C_0805_2012Metric,C15850,CL21A106KAYNNNE
1u 10V / 1u 50V,"C17,C18,C46",C_0603_1608Metric,C15849,CL10A105KB8NNNC
470n,"C40,C41",C_0603_1608Metric,C1623,CL10B474KA8NNNC
4.7u 50V,"C42,C49,C50,C51,C52",C_1206_3216Metric,C29823,1206B475K500NT
33p,C43,C_0603_1608Metric,C1663,CL10C330JB8NNNC
75p,C45,C_0603_1608Metric,C1681,0603CG750J500NT
10p,C67,C_0603_1608Metric,C1634,CL10C100JB8NNNC
SS34,D1,D_SMA,C8678,SS34
SMAJ15A,D2,D_SMA,C5353166,SMAJ15A
green,"D3,D5",LED_0603_1608Metric,C2986030,19-217/G7C-AN1P2/6T
BAV199,D4,SOT-23,C40919,"BAV199,215"
DFLS120L,"D6,D7",D_PowerDI-123,C155287,DFLS120L-7
BAT54,D8,D_SOD-323,C12744,LBAT54HT1G
2 A hold,F1,Fuse_1812_4532Metric,C2982282,ASMD1812-200-30V
470R 4A,FB1,L_1206_3216Metric,C703117,BLM31KN471SN1L
"12 V 2 A, floating",J1,BarrelJack_Horizontal,C720557,DC-005-A200
3.3u,L1,L_Bourns_SRP5030T,C189931,SRP5030T-3R3M
10u,L2,L_Taiyo-Yuden_NR-40xx,C18222009,MNR4018T100MT
15u,"L3,L4",L_Taiyo-Yuden_NR-40xx,C20612490,MNR4018T150MT
63.4k 1%,R1,R_0603_1608Metric,C2999593,FRC0603F6342TS
10k 1% / 10k,"R2,R3,R6,R24,R25,R26,R27,R46",R_0603_1608Metric,C25804,0603WAF1002T5E
12.4k,R4,R_0603_1608Metric,C861102,RT0603BRD0712K4L
2.37k,R5,R_0603_1608Metric,C705759,RT0603BRD072K37L
2.2k,R7,R_0603_1608Metric,C4190,0603WAF2201T5E
100 0.1%,R8,R_0603_1608Metric,C844889,TNPW0603100RBEEA
1k,R9,R_0603_1608Metric,C21190,0603WAF1001T5E
33,"R10,R18,R19",R_0603_1608Metric,C23140,0603WAF330JT5E
0,R17,R_0603_1608Metric,C21189,0603WAF0000T5E
4.7k,"R30,R31",R_0603_1608Metric,C23162,0603WAF4701T5E
105k,R32,R_0603_1608Metric,C16840,0603WAF1053T5E
15k,"R33,R34",R_0603_1608Metric,C22809,0603WAF1502T5E
120k,R35,R_0603_1608Metric,C25808,0603WAF1203T5E
200k,"R36,R41",R_0603_1608Metric,C25811,0603WAF2003T5E
1.3k,R37,R_0603_1608Metric,C22767,0603WAF1301T5E
1M,"R38,R42",R_0603_1608Metric,C22935,0603WAF1004T5E
51k,"R39,R43",R_0603_1608Metric,C23196,0603WAF5102T5E
75k,"R40,R45",R_0603_1608Metric,C23242,0603WAF7502T5E
19.6k,R44,R_0603_1608Metric,C22898,0603WAF1962T5E
TPS563208,U1,SOT-23-6,C468250,TPS563208DDCR
TPS7A8400A,U2,QFN-20-1EP_3.5x3.5mm_P0.5mm_EP2x2mm_ThermalVias,C524802,TPS7A8400ARGRR
LP38693MP-3.3,U3,SOT-223-5,C130904,LP38693MP-3.3/NOPB
TPS7A2033PDBV,U4,SOT-23-5,C2862740,TPS7A2033PDBVR
74LVC2G34,U5,SOT-363_SC-70-6,C426709,"74LVC2G34GW,125"
LT3471,U6,DFN-10-1EP_3x3mm_P0.5mm_EP1.65x2.38mm,C514422,LT3471EDD#TRPBF
LT3042xMSE,U7,MSOP-10-1EP_3x3mm_P0.5mm_EP1.68x1.88mm,C461518,LT3042EMSE#TRPBF
LT3093xMSE,U8,MSOP-12-1EP_3x4.039mm_P0.65mm_EP1.651x2.845mm,C670482,LT3093EMSE#PBF
LTC6655BHMS8-5,U9,MSOP-8_3x3mm_P0.65mm,C689432,LTC6655BHMS8-5#PBF
AD8676BRZ,U10,SOIC-8_3.9x4.9mm_P1.27mm,C206590,AD8676BRZ
AD5791BRUZ,U11,TSSOP-20_4.4x6.5mm_P0.65mm,C578299,AD5791BRUZ
AD8675ARZ,U12,SOIC-8_3.9x4.9mm_P1.27mm,C207408,AD8675ARZ
ISO7741DW,U13,SOIC-16W_7.5x10.3mm_P1.27mm,C571196,ISO7741DWR

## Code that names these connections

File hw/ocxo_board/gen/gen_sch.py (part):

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    # ------------------------------------------------------------ +-8 V from 3.3 V (LT3471), as the CN0531
    s.text(*g(6, 116), "DAC supplies, copied from the CN0531: LT3471 boost to +8 V and inverter to -8 V from +3V3_DAC")
    u6 = p("U6", "Regulator_Switching:LT3471", *g(30, 135))
    for pin, net in (("8", "+3V3_DAC"), ("9", "SS1"), ("7", "SS2"), ("10", "SW1"), ("6", "SW2"), ("1", "FB_P"),
                     ("2", "VREF_B"), ("3", "VREF_B"), ("4", "FB_N"), ("5", "GND"), ("11", "GND")):
        s.net(u6[pin], net)
    vert("C48", 8, 126, "10u 50V", C1206, "+3V3_DAC")
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    # ------------------------------------------------------------ +7.5 V (LT3042) and -7.5 V (LT3093)
    s.text(*g(84, 116), "+7.5 V (LT3042) and -7.5 V (LT3093), copied from the CN0531")
    u7 = p("U7", "Regulator_Linear:LT3042xMSE", *g(100, 128))
    for pin, net in (("1", "+8V"), ("2", "+8V"), ("3", "+8V"), ("4", "PG_P"), ("5", "ILIM_P"), ("6", "PGFB_P"),
                     ("7", "SET_P"), ("8", "GND"), ("11", "GND"), ("9", "+7V5"), ("10", "+7V5")):
        s.net(u7[pin], net)
    vert("R37", 88, 134, "1.3k", R0603, "ILIM_P")
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    vert("C50", 116, 126, "4.7u 50V", C1206, "+7V5")
    vert("R36", 120, 126, "200k", R0603, "+3V3_DAC", "PG_P")
    u8 = p("U8", "Regulator_Linear:LT3093xMSE", *g(100, 150))
    for pin, net in (("1", "-8V"), ("2", "-8V"), ("13", "-8V"), ("3", "-8V"), ("4", "PG_N"), ("5", "PGFB_N"),
                     ("6", "ILIM_N"), ("8", "SET_N"), ("9", "GND"), ("10", "-7V5"), ("11", "-7V5"), ("12", "-7V5")):
        s.net(u8[pin], net)
    s.nc(u8["7"])
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    # ------------------------------------------------------------ the DAC and its output buffer
    s.text(*g(166, 54), "AD5791 (RBUF = 1, unity gain, 0 to 5 V) and the AD8675 output buffer")
    u11 = p("U11", "Analog_DAC:AD5791xRUZ", *g(186, 72), value="AD5791BRUZ")
    for pin, net in (("3", "VREFP_S"), ("4", "VREFP_F"), ("16", "VREFN_F"), ("17", "VREFN_S"), ("1", "DAC_INV"),
                     ("20", "DAC_OUT"), ("2", "DAC_VOUT"), ("5", "+7V5"), ("18", "-7V5"), ("9", "+3V3_DAC"),
                     ("10", "+3V3_DAC"), ("15", "GND"), ("19", "GND"), ("12", "DAC_SDIN"), ("13", "DAC_SCLK"),
                     ("14", "DAC_SYNC"), ("11", "DAC_SDO"), ("8", "DAC_LDAC"), ("7", "DAC_CLR"), ("6", "DAC_RESET")):
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        else:
            s.nc(j8[n])
    u13 = p("U13", f"{NAME}:ISO7741DW", *g(36, 66), value="ISO7741DW")
    for pin, net in (("1", "ISO_3V3"), ("7", "ISO_3V3"), ("2", "ISO_GND"), ("8", "ISO_GND"), ("3", "PMOD_SDIN"),
                     ("4", "PMOD_SCLK"), ("5", "PMOD_SYNC"), ("6", "ISO_SDO"), ("16", "+3V3_DAC"), ("10", "+3V3_DAC"),
                     ("9", "GND"), ("15", "GND"), ("14", "DAC_SDIN"), ("13", "DAC_SCLK"), ("12", "DAC_SYNC"),
                     ("11", "DAC_SDO")):
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
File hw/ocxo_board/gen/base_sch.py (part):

"""The parts of the integrated OCXO board around its DAC section, for gen_sch.py: the 12 V input and its
protection, the buck converter to 5.6 V, the OCXO's 5 V regulator U2, the 3.3 V regulators U3 (+3V3_DAC) and U4
(+3V3_CLK), the tuning filter from DAC_OUT to the OCXO's tuning pin, the OCXO, and the 10 MHz buffer and its two
SMA outputs. gen_sch.py adds the DAC section and the SPI input from the RFSoC 4x2.

Positions are on a 2.54 mm grid, written as grid units through g(x, y).
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    s.net(c4["2"], "BUCK_SW")
    l1 = p("L1", "Device:L", *g(26, 29), 90, value="3.3u", fp="Inductor_SMD:L_Bourns_SRP5030T")
    s.join(u1["2"], g(22, 29), l1["1"])
    s.label(*g(22, 29), "BUCK_SW", 90)
    hang("C5", 31, 29, "22u 16V", C1206)
    hang("C6", 36, 29, "22u 16V", C1206)
    r1 = hang("R1", 41, 29, "63.4k 1%", R0603, bottom=None, lib="Device:R")
    r2 = p("R2", "Device:R", *g(41, 35), value="10k 1%", fp=R0603)
    s.join(r1["2"], g(41, 33), r2["1"])
    s.label(*g(41, 33), "BUCK_FB", 180)
    s.net(r2["2"], "GND")
    p("FB1", "Device:FerriteBead_Small", *g(47, 29), 90, value="470R 4A", fp="Inductor_SMD:L_1206_3216Metric")
    rail(29, 27.5, 29, 31, 36, 41, 46, flag_at=44)
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    r5 = p("R5", "Device:R", *g(104, 26.5), value="2.37k", fp=R0603)
    s.join(r4["2"], g(104, 24), r5["1"])
    s.join(c10["2"], g(108, 24), g(104, 24))
    s.label(*g(104, 24), "LDO_FB", 180)
    s.net(r5["2"], "GND")
    hang("R6", 112, 19, "10k", R0603, bottom="LDO_PG", lib="Device:R")
    r7 = hang("R7", 116, 19, "2.2k", R0603, bottom=None, lib="Device:R")
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    s.join(c21["1"], g(91, 58))
    s.join(c22["1"], g(96, 58))
    s.join(d4["3"], g(103, 58))
    s.label(*g(108, 58), "VCON", 0)
    s.nc(x1["2"])
    s.net(x1["3"], "+5V_OCXO")
    s.net(x1["5"], "GND")
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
